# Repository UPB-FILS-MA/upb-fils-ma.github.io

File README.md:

# MA Website

This is the website for the MA course delivered to ACS CC and FILS English.

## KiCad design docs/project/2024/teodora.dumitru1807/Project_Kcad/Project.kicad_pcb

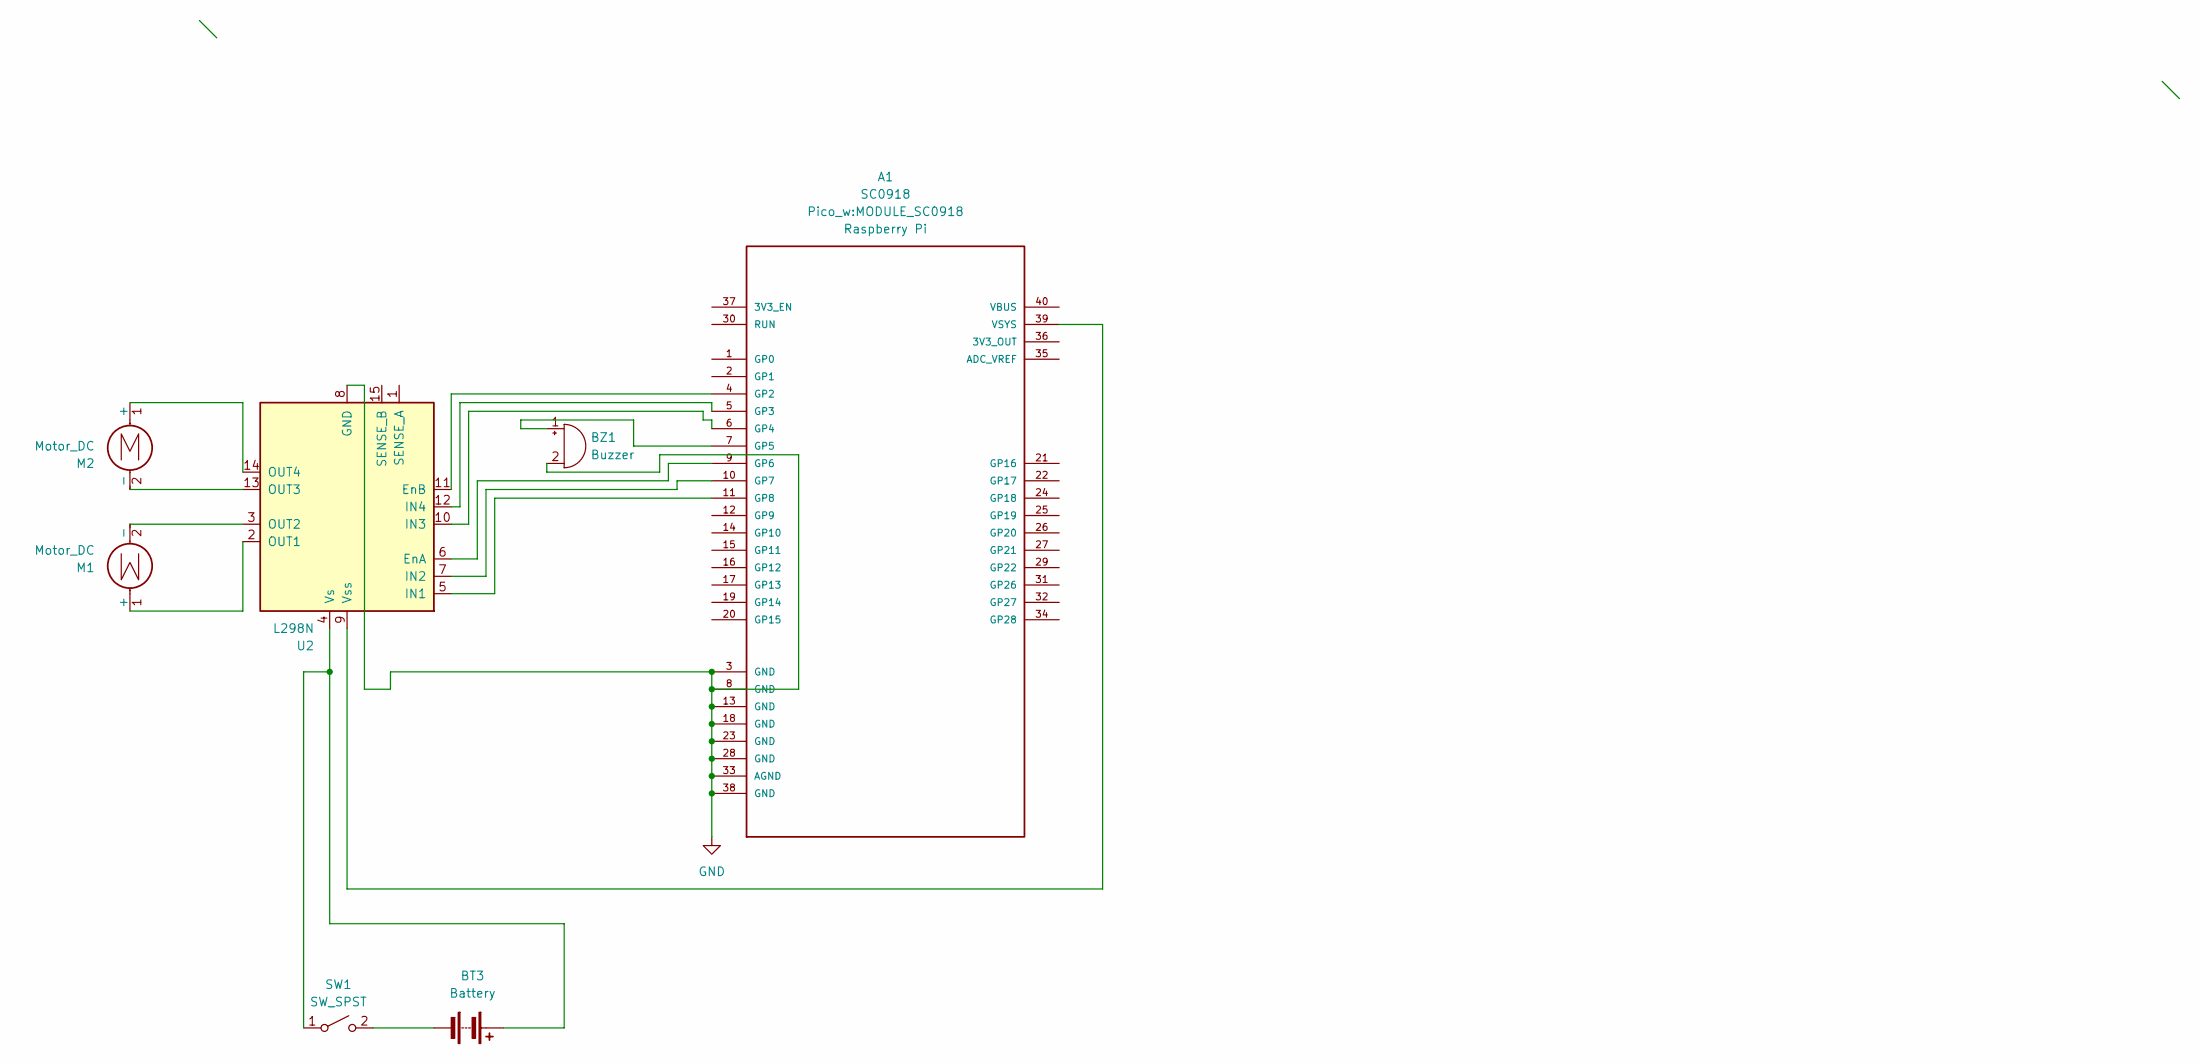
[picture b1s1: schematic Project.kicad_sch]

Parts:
A1: SC0918; MODULE_SC0918; PARTREV 1.6
BT3: Battery; BatteryHolder_Keystone_2462_2xAA
BZ1: Buzzer; Buzzer_12x9.5RM7.6
M1, M2: Motor_DC; Vybronics_VZ30C1T8219732L
SW1: SW_SPST; SW_DIP_SPSTx01_Slide_9.78x4.72mm_W8.61mm_P2.54mm
U2: L298N; TO-220-15_P2.54x2.54mm_StaggerOdd_Lead4.58mm_Vertical

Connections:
GND: A1.3 (GND), A1.8 (GND), A1.13 (GND), A1.18 (GND), A1.23 (GND), A1.28 (GND), A1.33 (AGND), A1.38 (GND), BZ1.2 (-), U2.8 (GND)
unnamed: A1.4 (GP2), U2.11 (EnB)
unnamed: A1.5 (GP3), U2.12 (IN4)
unnamed: A1.6 (GP4), U2.10 (IN3)
unnamed: A1.7 (GP5), BZ1.1 (+)
unnamed: A1.9 (GP6), U2.6 (EnA)
unnamed: A1.10 (GP7), U2.7 (IN2)
unnamed: A1.11 (GP8), U2.5 (IN1)
unnamed: A1.39 (VSYS), U2.9 (Vss)
unnamed: BT3.1 (+), SW1.1 (A), U2.4 (Vs)
unnamed: BT3.2 (-), SW1.2 (B)
unnamed: M1.1 (+), U2.2 (OUT1)
unnamed: M1.2 (-), U2.3 (OUT2)
unnamed: M2.1 (+), U2.14 (OUT4)
unnamed: M2.2 (-), U2.13 (OUT3)

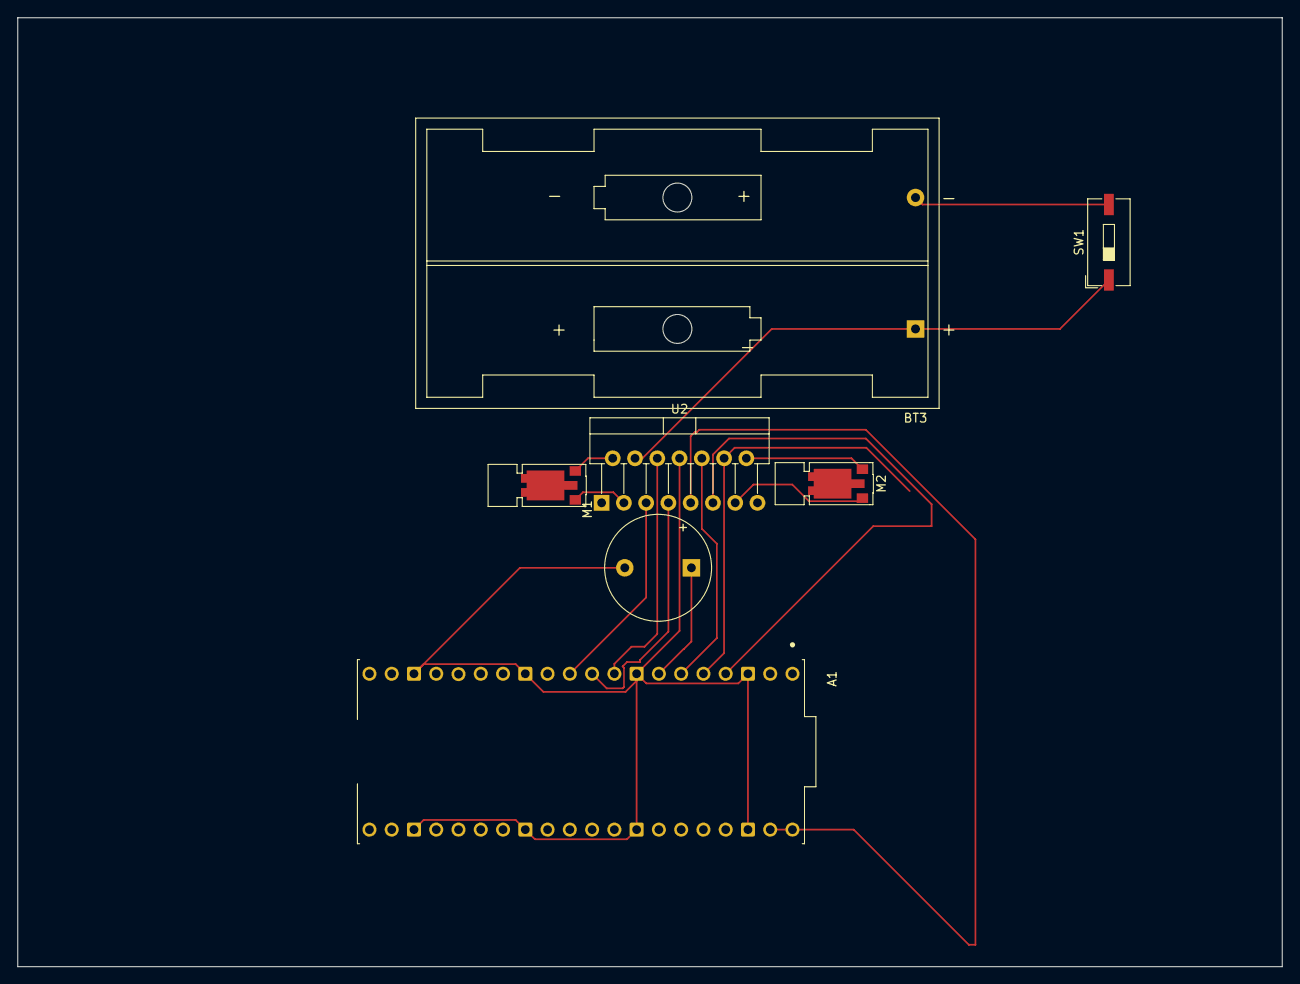
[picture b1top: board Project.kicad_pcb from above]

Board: 2 copper layers, 144.2 x 108.2 mm, 7 parts (0 on the bottom side), 15 nets.

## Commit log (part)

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2024-05-20 Added Hardware photos and edited Kicad Schematic (#406)
    * Project Docummentation
    * Update docs/project/2024/matei_teodor.petrec/index.md
    * Added Kicad Schematic
    * Added Hardware pictures and edited kicad schematic
    ---------
2024-05-20 deploy: 3ff1254038913443c3263f203fa85649d4246b3b
2024-05-20 Create test
2024-05-20 teodora.chirila-Update documentation
2024-05-20 Fixing something in the logs (#407)
    * Update index.md
    * Update index.md
2024-05-20 removed accidental slash after schematics subtitle (#409)
2024-05-20 Added The whole project , 2nd kicad scheme wrong
    I posted the whole folder again. I had a previous kicad file that was incomplete, added the new one and didn't know how to delete the first one, so I deleted the entire directory and re added
2024-05-20 deploy: 118f772cda2ba306b42ad9a6949174e0a32a96be
2024-05-20 deploy: 496656524517dd55c62e91799fd198751af80b37
2024-05-20 deploy: ce4a5bd0bea08ebb1f183447b00645a373846c70
2024-05-20 deploy: d131202548ac82282221d6b085e046018ba71b3d
2024-05-20 Finished Hardware milestone
2024-05-20 Finished Hardware milestone (#414)
2024-05-20 Project documentation (#315)
    * Project Documentation
    * Feedback Update index.md
    * Updated Project files
    This now includes the Kicad schematic (a screenshot and the actual file), and two photos featuring the components and the assembled project
    * Hardware documentation update
    Renamed two files to exclude spaces, replaced them with "_". Also removed a kicad file
2024-05-20 deploy: 82afcd94d71eb35e63eea3456c99c80947cff9b3
2024-05-20 Fixed hardware photos not displaying due to wrong extension type (it was .png) and changed to .jpg
2024-05-21 I have uploaded the project name.
2024-05-23 deploy: 6e38d46a447ff1f6f8c7686a022dfa870b0bb010
2024-05-23 All done
2024-05-23 Solved
2024-05-24 Added final touches
2024-05-24 Fixed build errors
2024-05-24 deploy: 5a1186c5779a5414afac142c29acce73a73c6f6b
2024-05-25 Rename hardware (1).jpeg to hardware(1).jpeg
2024-05-25 Rename hardware (3).jpeg to hardware(3).jpeg
2024-05-25 Changed hardware test pics with working game pics.
2024-05-25 Rename kicad_schematic22.png to kicad_schematic222.png
2024-05-26 Update index.md
    updated cyw43
2024-05-26 Update index.md and software
2024-05-26 update log
2024-05-26 Rename docs/project/2024/mohamad_mario.sakka/kicad_schematic222.png to docs/project/2024/mohamad_mario.sakka/hardware_pics/kicad_schematic222.png
2024-05-26 Rename docs/project/2024/mohamad_mario.sakka/Pic_2.jpg to docs/project/2024/mohamad_mario.sakka/hardware_pics/pic_2.jpg
2024-05-26 Rename docs/project/2024/mohamad_mario.sakka/coolingpad.jpg to docs/project/2024/mohamad_mario.sakka/hardware_pics/coolingpad.jpg
2024-05-26 finishing touches + hardware update
2024-05-26 Finished all project
2024-05-26 Finished everything_2
2024-05-26 log and software update
2024-05-26 added software files
2024-05-26 Final update
2024-05-26 Last week milestone added
2024-05-26 complete the logs and libraries and add final project photos
2024-05-26 Finished Project Documentation
2024-05-26 Updated the log for the last week
2024-05-27 Final update to documentation
2024-05-27 software milestone files
2024-05-27 software
2024-05-27 Added software
2024-05-27 Added last week's progress
2024-05-27 Software
    final review
2024-05-27 software milestone
    software
2024-05-27 updated logs
2024-05-28 update image reference
2024-05-28 deleted conflicted files
2024-05-28 renamed images and modified index.md
2024-05-28 fixed pull request
2024-05-29 The updated version of the project
    After the PM Fair I made a few changes to better represent my finished project.
2024-05-31 made some final adjustments
2024-06-09 Updated the Log section (#437)
    * Add files via upload
    * Rename project_architecture.svg to project_architecture_light_mode.svg
    * Update index.md
    * Delete docs/project/2024/azzam.zafar/project_architecture_dark_mode.svg
    * Add files via upload
    * Rename my_project_architecture_dark_mode.svg to project_architecture_dark_mode.svg
2024-06-09 deploy: 7495deca691b861e26961303ee671506bbd970ac
2024-06-09 Project documentation (#444)
    * Added index.md
    * Added your_curs_upb_ro_id.md
    * Update index.md
    * Add files via upload
    * Rename pic srvo.png to Architecture.png
    * Update index.md
2024-06-09 Software Milestone (#454)
    * Project Update
    * Update index.md
    * Update index.md
    * Update docs/project/2024/cristian.iacobescu/index.md
    * hardware update
    kicad update plus description
2024-06-09 Software milestone (#457)
    * Create index.md
    * WIFIrobotcar_documentation
    * Project_documentation_wificar
    * project_documentation
    * project_documentation
    * project_documentation
2024-06-09 Updated the log for the last week (#461)
2024-06-09 deploy: 7a616cfcd21b2ad6ebfe7e6a76057bba631dfc5d
2024-06-09 deploy: f40dff8829ad809d3754f6f497b501c109b229c8
2024-06-09 deploy: f02f6c399fe716a98137139c8b1eef52388aae6c
2024-06-09 added links for the software update
2024-06-09 Project documentation- Final changes (#433)
    * Update index.md
    * Update index.md
    * Update index.md
    * Update index.md
    * Delete docs/project/2024/mohamad_mario.sakka/kicad_schematic22.png
    * Add files via upload
2024-06-09 Made some final modifications (#492)
    * added the project documentation
    * Update index.md
    * Update index.md
    * Update index.md
    * Update index.md
    * remove duplicate PR
2024-06-09 Final updates (#489)
    * hardware milestone additions
    * hardware branch small fix
    * added logs and extra photo
2024-06-09 Logs update (#486)
    * Create index.md
    * Add files via upload
    * Delete docs/project/2024/ana_alexia.alecu/index.md
    * Rename your_curs_upb_ro_id.md to index.md
    * Update index.md
    * Add files via upload
2024-06-09 Final update (#481)
    * documentation
    project documentation
    * update
    * hardware milestone
    hardware
    * fixed kicad schematic
2024-06-09 final project documenatation (#475)
    * Add files via upload
    * Update index.md
    * Delete docs/project/2024/miruna.solomon/pacman_game.kicad_sch
    * Delete docs/project/2024/miruna.solomon/remote_game.kicad_sch
    * Add files via upload
    * Add files via upload
2024-06-09 Added last week's progress (#473)
2024-06-09 Added software (#471)
2024-06-09 Updated log (#468)
    * Update index.md
    * Add files via upload
    * Update index.md
    * Update index.md
    * Update index.md
2024-06-09 [Crasher game] Software Milestone & Logs (#465)
    * software milestone files
    * update image reference
2024-06-09 Final update (#450)
2024-06-09 added the log (#447)
    * Ferrari Line Follower and Obstacle Avoider Car_Documentation
    * maria.ionescu_Documentation
    * update index.md
    * Ferrari Line Follower and Obstacle Avoider Car_Documentation
    * Update index.md
    * Update index.md
2024-06-09 final revision of project (#435)
    * updated hardware schematic + fixes
    * finished hardware milestone + changes
    * actually add the hardware milestone
    * move .sch file to project repo
    * finishing touches + hardware update
2024-06-09 Final patch (#441)
    * Add files via upload
    * Update index.md
    * Update index.md
2024-06-09 Add week 3 progress (alberto.udrea0412) (#430)
    * opted for a more reliable syntax - photo section
    * added a simpler version of the kicad
    * added missing file format
    * moved the photos into a table - better design
    * Added Week 3 progress
2024-06-09 Software milestone documentation update (#425)
    * documentation
    * Update eduard.matei2905.md
    * Update eduard.matei2905.md
    * Update and rename eduard.matei2905.md to index.md
    * Update index.md
    * Add files via upload
2024-06-09 deploy: 89e5a4b958adaa91e61047032287aabc81f29b10
2024-06-09 deploy: 3ae13727033f7a8737e982df9a8da6669ad327c6
2024-06-09 deploy: 434dd8655429d468612be504581b9663c531689e
2024-06-09 deploy: 229b9b3a721559e8ac418ccf1b6ede474ce61fc2
2024-06-09 deploy: 0f0a33e172944432ca705a8a2bd9eef760168ac0
2024-06-09 Update index.md
    Fixed some typos.
2024-06-09 Added more images of the hardware (#426)
    * Added project hardware schematic
    * Delete docs/project/2024/robert.leonte directory
    * Add files via upload
    * Update index.md
2024-06-09 deploy: f273142bee709533c767d542cd321859eb97ad0c
2024-06-09 Changes in the Project Documentation (#424)
    * Create index.md
    * Add files via upload
    * Delete docs/project/2024/ramona.nitu
    * Add files via upload
    * Update index.md
    * Update index.md
2024-06-09 deploy: 98032f8264ed410d33f11cdee30d0a57836ce664
2024-06-09 Update index.md (#495)
    Fixed some typos.
2024-06-09 software milestone (#478)
    * Completed some the index
    * Update index.md
    * Update docs/project/2024/Ruxandra.popa/index.md
    * Update index.md
    * Update index.md
    * Update index.md
2024-06-09 Project documentation (#451)
    * project documentation
    project
    * reset la original
    * documentatie antonio
    lalalalala
    * schimbarile finale
2024-06-09 log and software update (#439)
2024-06-09 Finished Project + Software Milestone (#423)
    * Changed hardware test pics with working game pics.
    * Update index.md
    * Update index.md
2024-06-09 deploy: 71c3bac9aa1dcd444aa5cff896d926906299dbf2
2024-06-09 deploy: 565cc328d767ac72ad13181606585c50f4196c6a
2024-06-09 Project hardware (#420)
    * test commit
    * first commit
    * Update index.md
    * Update index.md
    * added kicad schematic
    * added kicad schematic
2024-06-09 deploy: 8cb201c913be1719ee27e2614214ef9461f7076a
2024-06-09 deploy: 08a01126842a274800092bd71c270c536ba198ff
2024-06-10 Project update lita naomi fixed (#497)
    * update
    kicad, pictures, and hardware description added
    * image type corrected
    * changed links
    links for motor and module changed
    * added the changes
2024-06-10 Project update chiorean rebeca (#496)
    * Chiorean Rebeca Hardware Milestone
    This is the hardware milestone and the improved version of the documentation
    * Update index.md
    made a few changes regarding grammar and added more to the "Motivation" section
    * Updated the architecture picture
    made sure that everything is nice and neat.
2024-06-10 deploy: 720bc51adaa4cd8394e0c26c14080847848d4b5c
2024-06-10 deploy: 5bbce0a2c25a17ab34da09ea80e52cd7a68fb77d
2024-06-10 Hardware2
2024-06-11 deploy: d2f0e891828c294693193a38e0df77a4fb665af8
2024-06-27 projects
2024-06-27 demo gif
2024-08-06 Update index.md
    changed project (still need to add the hardware image )
2024-08-26 I added a picture
2024-09-03 Update index.md for hardware milestone
2024-09-04 New project's documentation (#500)
    Added the new project's documentation.
2024-09-04 deploy: 126036df0ec3155b7c239a0b3ee2e944b032f333
2024-09-04 deploy: 8cf32cdcebbf3a668c0faa8716b38ccf6856ca63
2025-02-06 run workflow
2025-02-06 integrate slides and update links
2025-02-06 build in bash
2025-02-06 stop the workflow for push
2025-02-07 Two series (#502)
    * add both series
    * run workflow
    * workflow
    * integrate slides and update links
    * fix workflow
    * build in bash
2025-02-07 update deploy workflow (#505)
2025-02-11 update repository links
2025-02-11 add slides for lecture 01 and 02
2025-02-11 add pages action
2025-02-11 add read permission
2025-02-11 update link
2025-02-11 deploy: dec106d6708bc969a46996eaff6e36c488405a21
2025-02-12 add rp2040 gpio input output path
2025-02-12 improve rust code to extract bits to make it more readable and copyable
2025-02-12 slides 01
2025-02-12 11 feb primele sub dupa merge
2025-02-12 use cache for used modules
2025-02-12 fix path
2025-02-12 deploy: ffbf9eef1a3a374bb60ae03efd237b03e060aeba
